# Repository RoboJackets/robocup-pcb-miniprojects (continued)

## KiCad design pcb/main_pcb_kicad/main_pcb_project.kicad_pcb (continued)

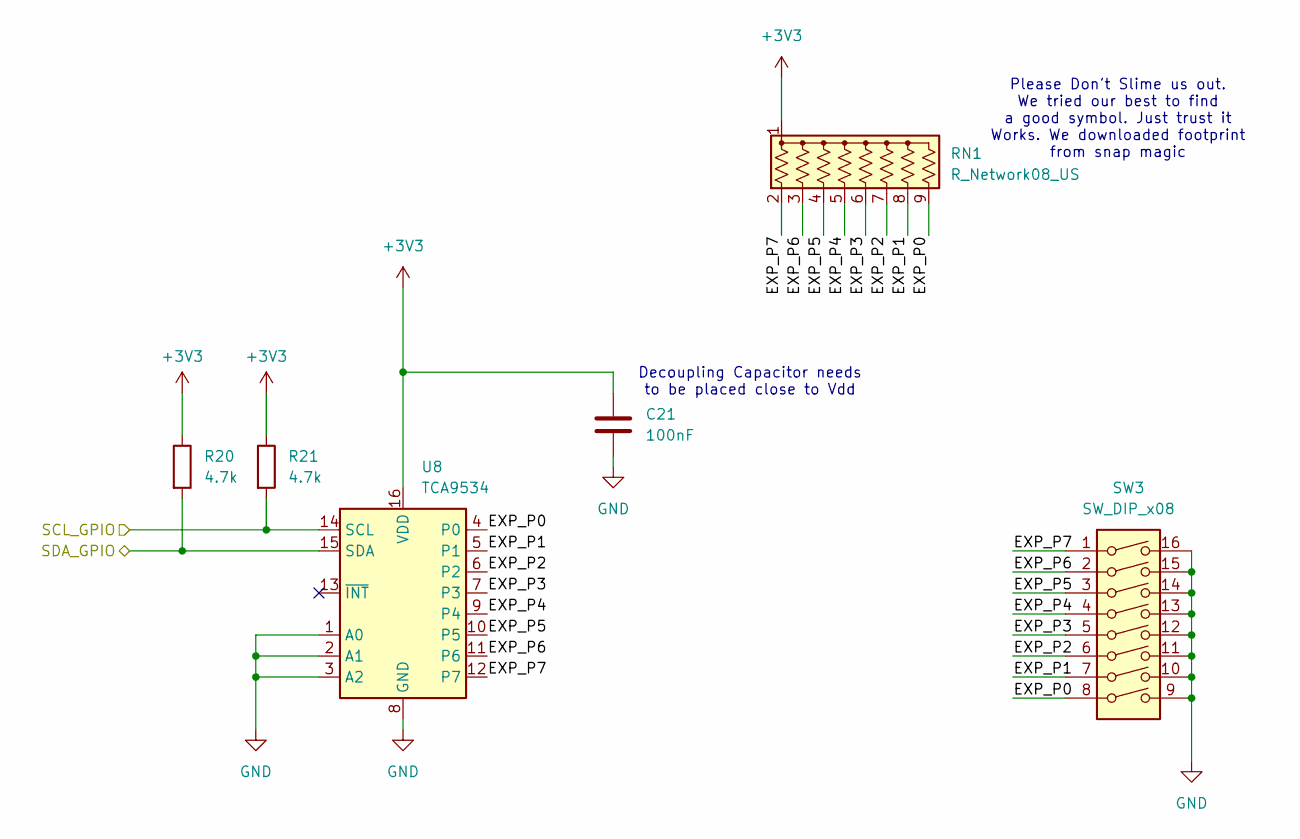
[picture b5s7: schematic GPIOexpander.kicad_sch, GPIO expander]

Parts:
C21: 100nF; C_0603_1608Metric; Manufacturer P/N CL10B104KB8NNNC
R20, R21: 4.7k; R_0402_1005Metric; Manufacturer P/N RC0402FR-074K7L
RN1: R_Network08_US; YC158_RNet08; Manufacturer P/N RC0402FR-074K7L
SW3: SW_DIP_x08; SW_DIP_SPSTx08_Slide_9.78x22.5mm_W7.62mm_P2.54mm; Manufacturer P/N DS01C-254-L-08BE
U8: TCA9534; TSSOP-16_4.4x5mm_P0.65mm; Manufacturer P/N TCA9534PWR

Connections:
+3V3: C21.1, R20.1, R21.1, RN1.1 (common), U8.16 (VDD); also elsewhere on the board
/GPIO expander/EXP_P0: RN1.9 (R8), SW3.8, U8.4 (P0)
/GPIO expander/EXP_P1: RN1.8 (R7), SW3.7, U8.5 (P1)
/GPIO expander/EXP_P2: RN1.7 (R6), SW3.6, U8.6 (P2)
/GPIO expander/EXP_P3: RN1.6 (R5), SW3.5, U8.7 (P3)
/GPIO expander/EXP_P4: RN1.5 (R4), SW3.4, U8.9 (P4)
/GPIO expander/EXP_P5: RN1.4 (R3), SW3.3, U8.10 (P5)
/GPIO expander/EXP_P6: RN1.3 (R2), SW3.2, U8.11 (P6)
/GPIO expander/EXP_P7: RN1.2 (R1), SW3.1, U8.12 (P7)
/SCL_GPIO: R21.2, U8.14 (SCL); also elsewhere on the board
/SDA_GPIO: R20.2, U8.15 (SDA); also elsewhere on the board
GND: C21.2, SW3.9, SW3.10, SW3.11, SW3.12, SW3.13, SW3.14, SW3.15, SW3.16, U8.1 (A0), U8.2 (A1), U8.3 (A2), U8.8 (GND); also elsewhere on the board

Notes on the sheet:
Decoupling Capacitor needs to be placed close to Vdd
Please Don't Slime us out. We tried our best to find a good symbol. Just trust it Works. We downloaded footprint from snap magic

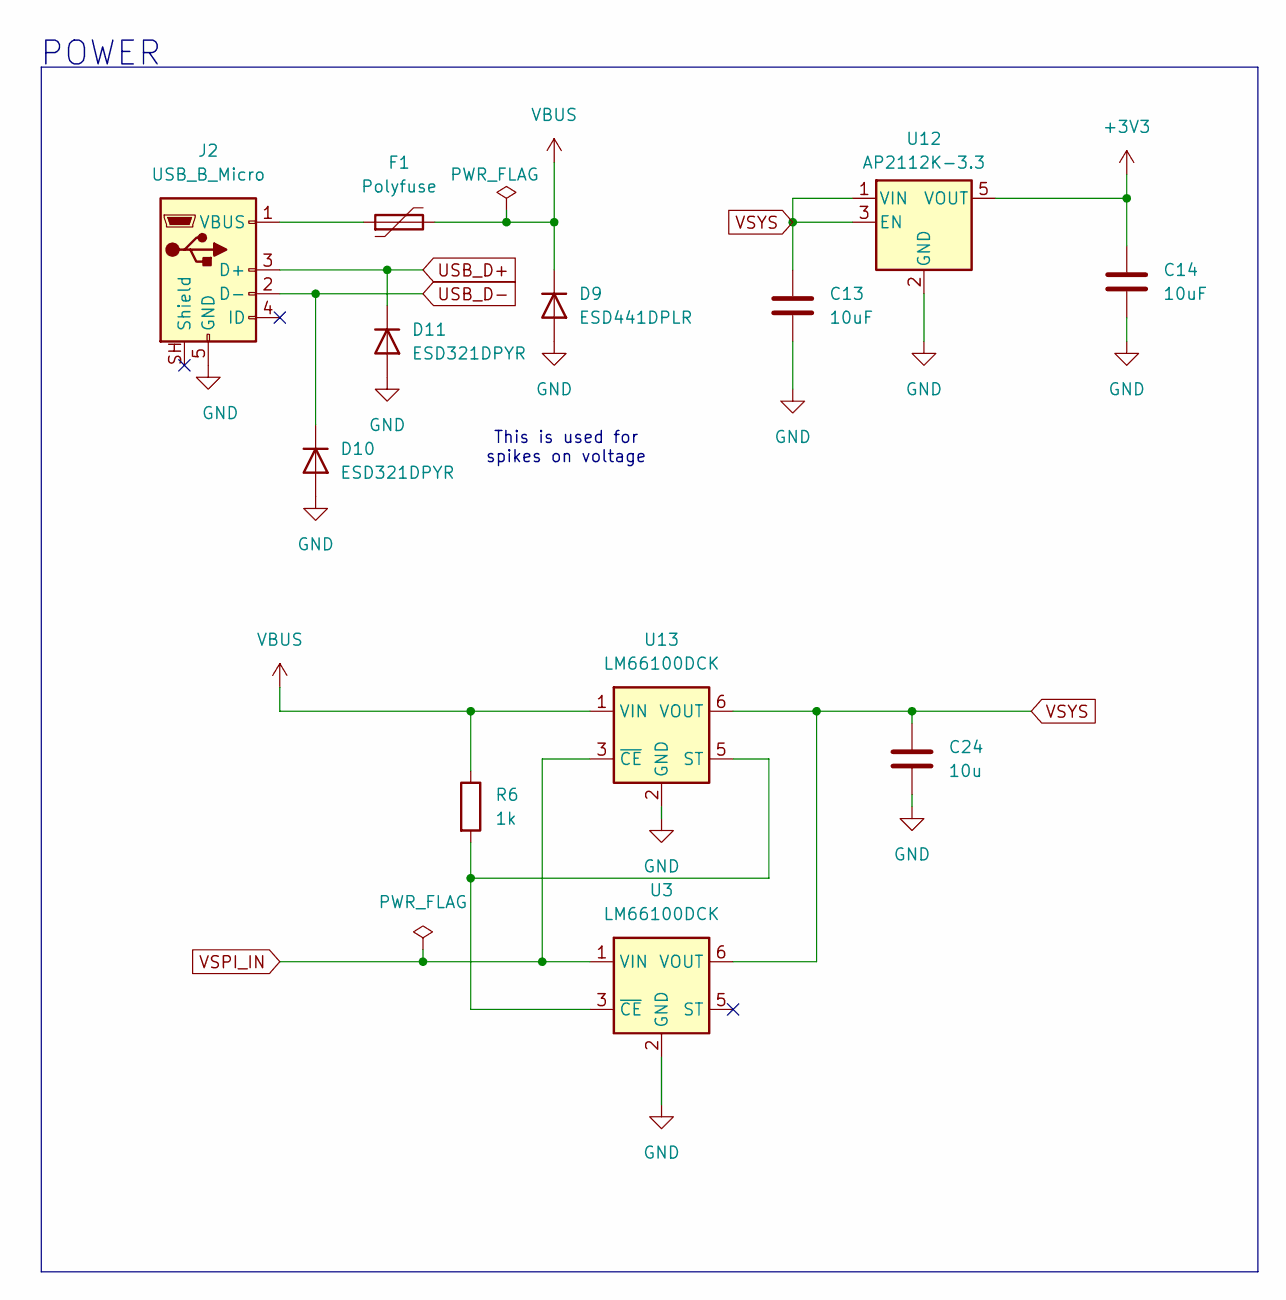
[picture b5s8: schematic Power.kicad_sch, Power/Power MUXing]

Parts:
C13, C14: 10uF; C_0402_1005Metric; Manufacturer P/N C0805C106M4PACTU
C24: 10u; C_0402_1005Metric; Manufacturer P/N C0805C106M4PACTU
D9: ESD441DPLR; D_0201_0603Metric; Manufacturer P/N ESD441DPLR
D10, D11: ESD321DPYR; D_0402_1005Metric; Manufacturer P/N ESD351DPYR
F1: Polyfuse; Fuse_1206_3216Metric; Manufacturer P/N 0ZCJ0050FF2G
J2: USB_B_Micro; USB_Micro-B_Amphenol_10118194_Horizontal; Manufacturer P/N 10118194-0001LF
R6: 1k; R_0402_1005Metric; Manufacturer P/N RC0402FR-071KL
U3, U13: LM66100DCK; SOT-363_SC-70-6; Manufacturer P/N LM66100DCKR
U12: AP2112K-3.3; SOT-23-5; Manufacturer P/N AP2112K-3.3TRG1

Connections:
+3V3: C14.1, U12.5 (VOUT); also elsewhere on the board
GND: C13.2, C14.2, C24.2, D9.2 (A), D10.2 (A), D11.2 (A), J2.5 (GND), U3.2 (GND), U12.2 (GND), U13.2 (GND); also elsewhere on the board
unnamed: F1.1, J2.1 (VBUS)
unnamed: R6.2, U3.3 (~CE), U13.5 (ST)
USB_D+: D11.1 (K), J2.3 (D+); also elsewhere on the board
USB_D-: D10.1 (K), J2.2 (D-); also elsewhere on the board
VBUS: D9.1 (K), F1.2, R6.1, U13.1 (VIN); also elsewhere on the board
VSPI_IN: U3.1 (VIN), U13.3 (~CE); also elsewhere on the board
VSYS: C13.1, C24.1, U3.6 (VOUT), U12.1 (VIN), U12.3 (EN), U13.6 (VOUT); also elsewhere on the board

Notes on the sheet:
POWER
This is used for spikes on voltage

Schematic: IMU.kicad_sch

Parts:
C15: 0.1uF; C_0603_1608Metric; Manufacturer P/N CL10B104KB8NNNC
C16: 2.2uF; C_0603_1608Metric; Manufacturer P/N CL10B225KP8NNNC
C17: 10nF; C_0603_1608Metric; Manufacturer P/N CL10B103KB8NNNC
R12, R13: 4.7k; R_0402_1005Metric; Manufacturer P/N RC0402FR-074K7L
U4: ICM-42605; LGA14_2P5X3X0P91_IVS-L; Manufacturer P/N ICM-42605

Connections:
+3V3: C15.1, C16.1, C17.1, R12.1, R13.1, U4.5 (VDDIO), U4.8 (VDD), U4.12 (AP_CS); also elsewhere on the board
/SCL_IMU: R12.2, U4.13 (AP_SCL/AP_SCLK); also elsewhere on the board
/SDA_IMU: R13.2, U4.14 (AP_SDA/AP_SDIO/AP_SDI); also elsewhere on the board
GND: C15.2, C16.2, C17.2, U4.1 (AP_SDO/AP_AD0), U4.6 (GND), U4.7 (RESV), U4.9 (INT2/FSYNC); also elsewhere on the board

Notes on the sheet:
These are pull up resistors
Please don't slime us out. We tried our best to make another design but things happened and we were unable Sorry :(
These capacitors need to be placed close to Vdd
Place capacitor close to VDDIO

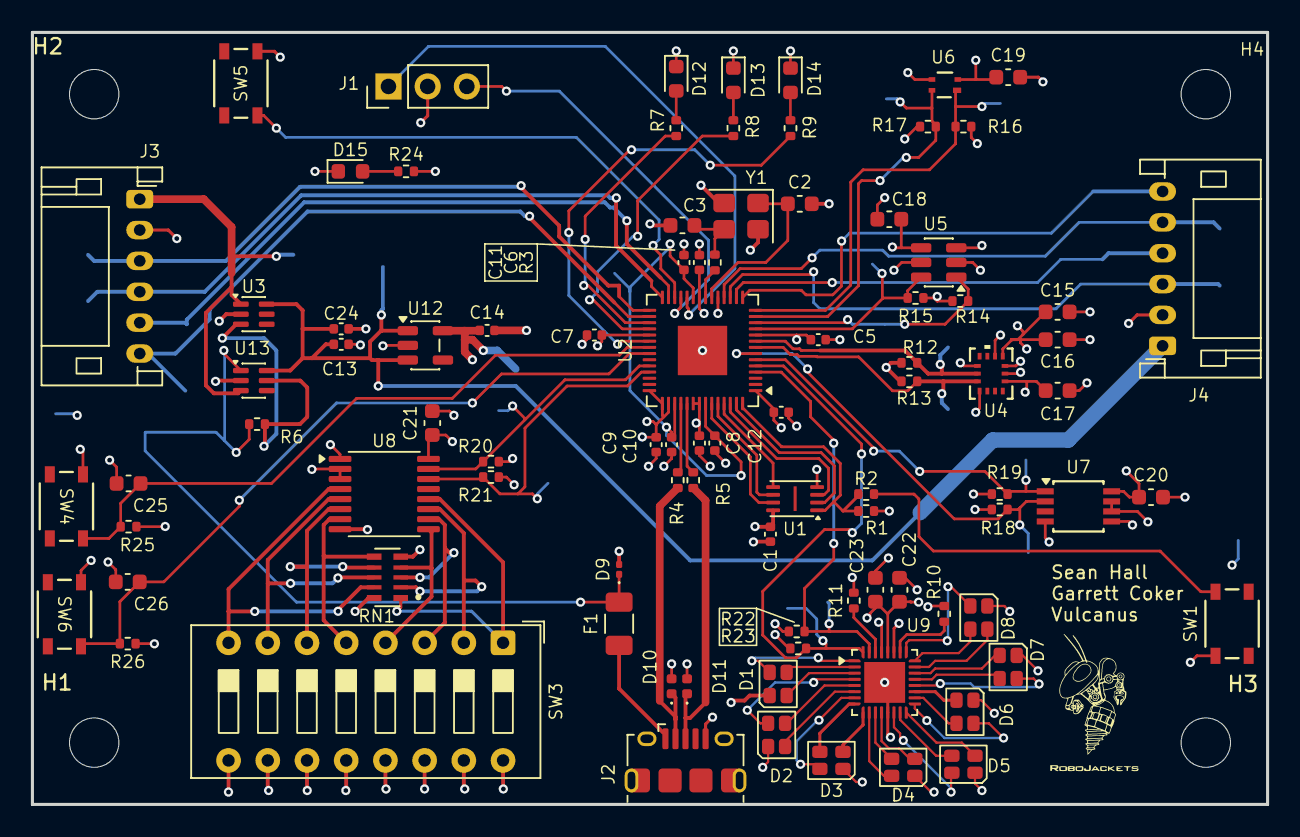
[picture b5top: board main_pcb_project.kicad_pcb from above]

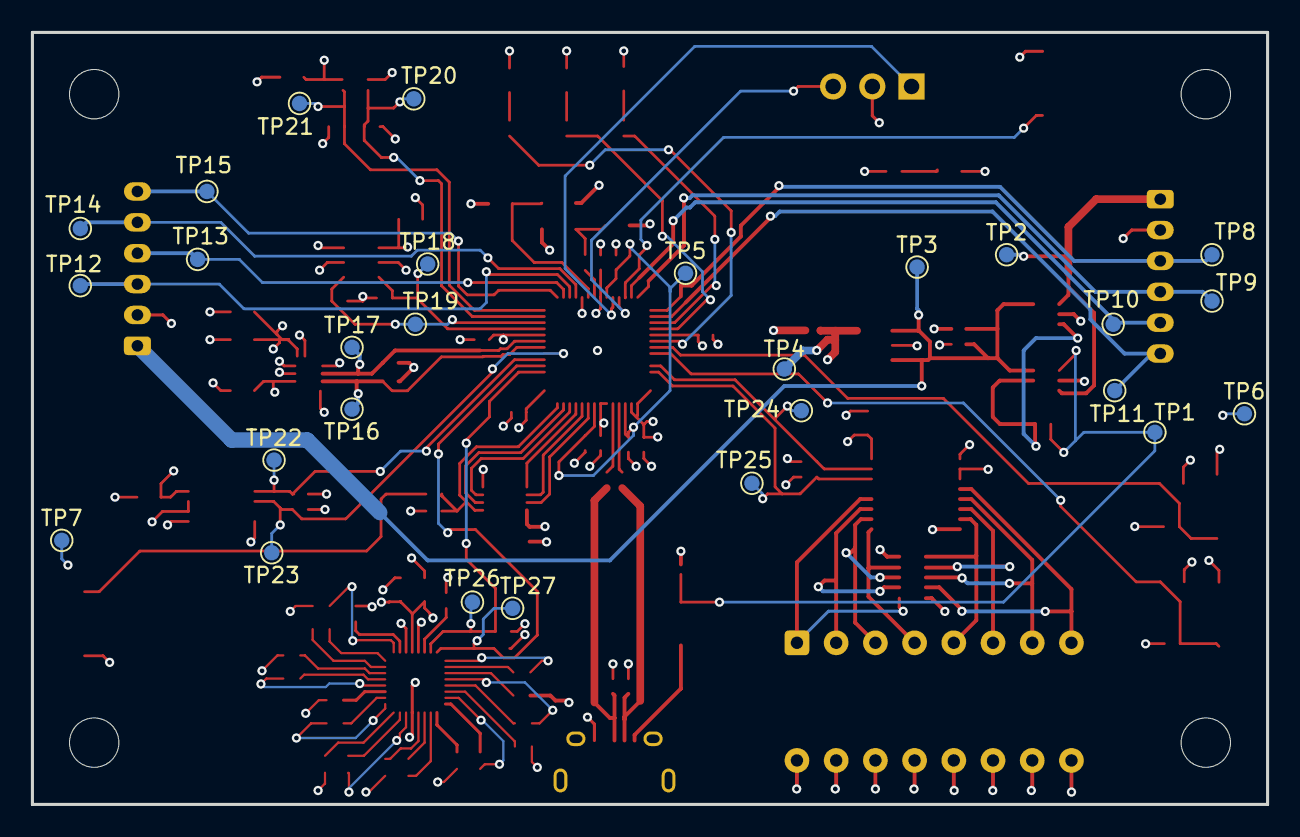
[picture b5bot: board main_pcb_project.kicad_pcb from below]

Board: 4 copper layers, 80.0 x 50.0 mm, 121 parts (27 on the bottom side), 88 nets.

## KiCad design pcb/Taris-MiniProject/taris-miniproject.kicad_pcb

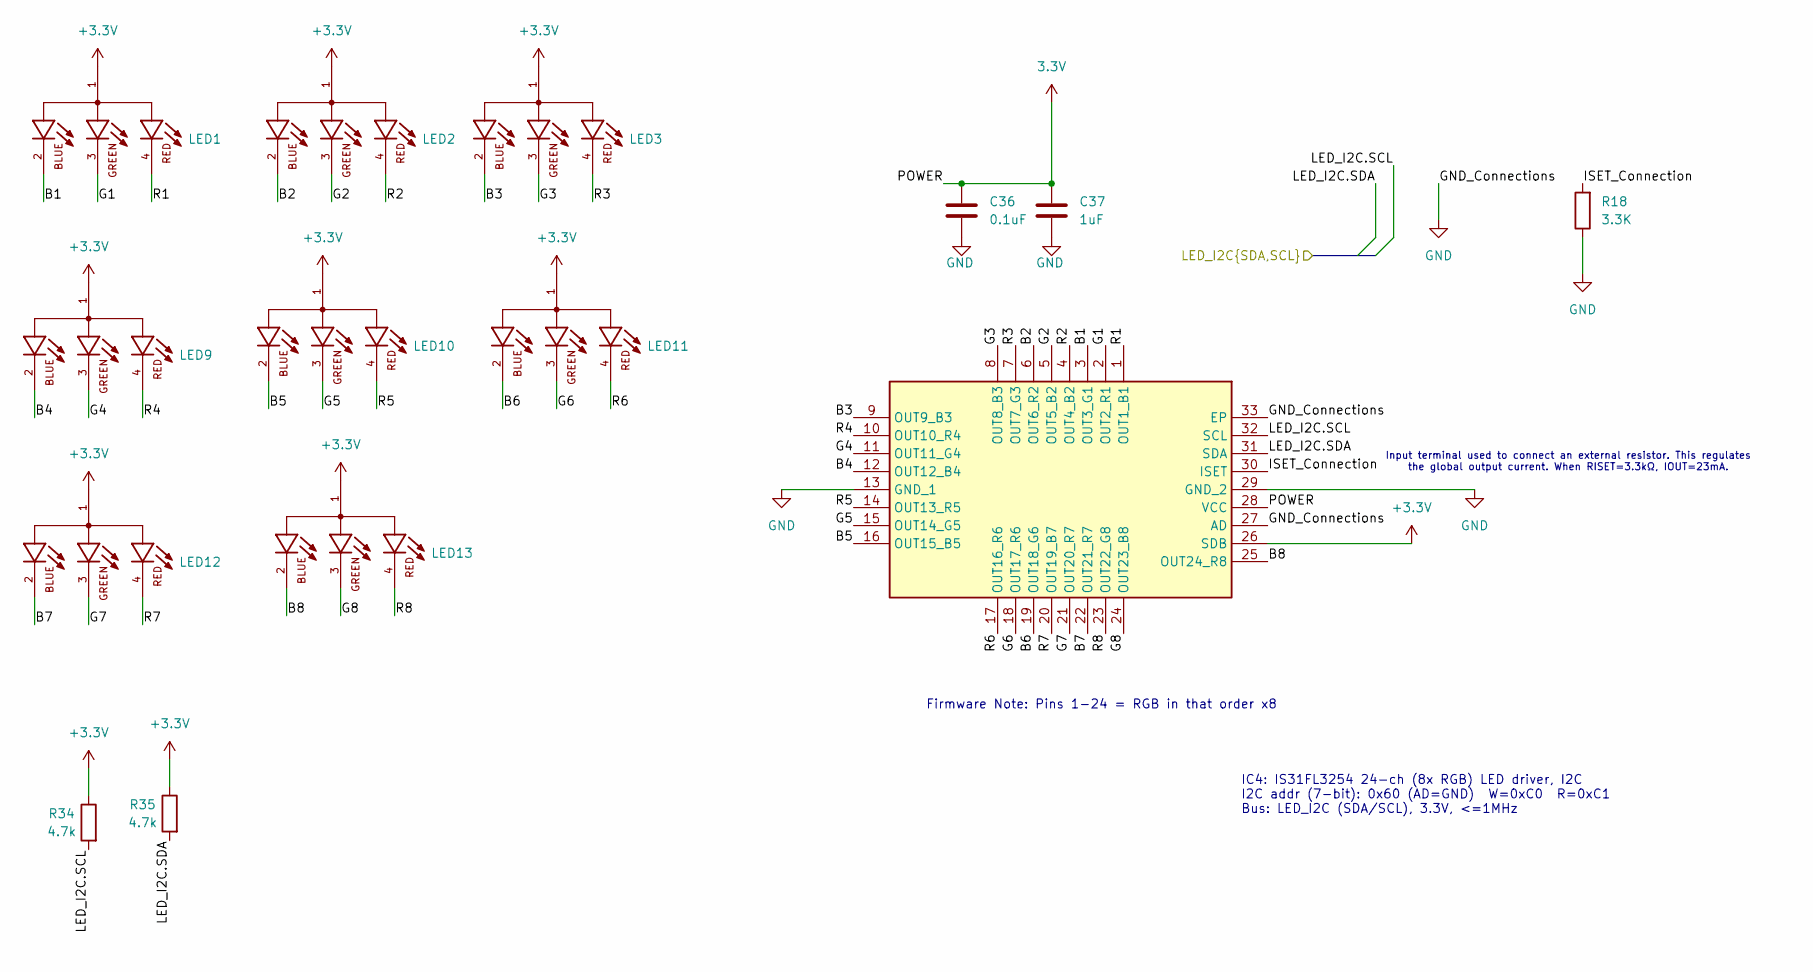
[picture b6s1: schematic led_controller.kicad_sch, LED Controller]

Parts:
C36: 0.1uF; C_0603_1608Metric; Manufacturer P/N CC0603KRX5R8BB104
C37: 1uF; C_0603_1608Metric; Manufacturer P/N GMC04X7R105K10NT
IC4: IS31FL3254-QFLS4-TR; QFN40P400X400X80-33N-D; Manufacturer_Part_Number IS31FL3254-QFLS4-TR
LED1, LED2, LED3, LED9, LED10, LED11, LED12, LED13: CLMVC-FKA-CL1D1L71BB7C3C3; LED_CLMVC-FKA-CL1D1L71BB7C3C3; PARTREV 14; DigiKey_Part_Number CLMVC-FKA-CL1D1L71BB7C3C3CT-ND
R18: 3.3K; R_0603_1608Metric; Manufacturer P/N RC0603FR-073K3L
R34, R35: 4.7k; R_0402_1005Metric; Manufacturer P/N RC0402FR-134K7L

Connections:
3.3V: C36.1, C37.1, IC4.28 (VCC); also elsewhere on the board
+3.3V: IC4.26 (SDB), LED1.1, LED2.1, LED3.1, LED9.1, LED10.1, LED11.1, LED12.1, LED13.1, R34.1, R35.1; also elsewhere on the board
/LED Controller/B1: IC4.3 (OUT3_G1), LED1.2
/LED Controller/B2: IC4.6 (OUT6_R2), LED2.2
/LED Controller/B3: IC4.9 (OUT9_B3), LED3.2
/LED Controller/B4: IC4.12 (OUT12_B4), LED9.2
/LED Controller/B5: IC4.16 (OUT15_B5), LED10.2
/LED Controller/B6: IC4.19 (OUT18_G6), LED11.2
/LED Controller/B7: IC4.22 (OUT21_R7), LED12.2
/LED Controller/B8: IC4.25 (OUT24_R8), LED13.2
/LED Controller/G1: IC4.2 (OUT2_R1), LED1.3
/LED Controller/G2: IC4.5 (OUT5_B2), LED2.3
/LED Controller/G3: IC4.8 (OUT8_B3), LED3.3
/LED Controller/G4: IC4.11 (OUT11_G4), LED9.3
/LED Controller/G5: IC4.15 (OUT14_G5), LED10.3
/LED Controller/G6: IC4.18 (OUT17_R6), LED11.3
/LED Controller/G7: IC4.21 (OUT20_R7), LED12.3
/LED Controller/G8: IC4.24 (OUT23_B8), LED13.3
/LED Controller/ISET_Connection: IC4.30 (ISET), R18.2
/LED Controller/R1: IC4.1 (OUT1_B1), LED1.4
/LED Controller/R2: IC4.4 (OUT4_B2), LED2.4
/LED Controller/R3: IC4.7 (OUT7_G3), LED3.4
/LED Controller/R4: IC4.10 (OUT10_R4), LED9.4
/LED Controller/R5: IC4.14 (OUT13_R5), LED10.4
/LED Controller/R6: IC4.17 (OUT16_R6), LED11.4
/LED Controller/R7: IC4.20 (OUT19_B7), LED12.4
/LED Controller/R8: IC4.23 (OUT22_G8), LED13.4
/LED_I2C.SCL: IC4.32 (SCL), R34.2; also elsewhere on the board
/LED_I2C.SDA: IC4.31 (SDA), R35.2; also elsewhere on the board
GND: C36.2, C37.2, IC4.13 (GND_1), IC4.27 (AD), IC4.29 (GND_2), IC4.33 (EP), R18.1; also elsewhere on the board

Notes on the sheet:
Firmware Note: Pins 1-24 = RGB in that order x8
IC4: IS31FL3254 24-ch (8x RGB) LED driver, I2C I2C addr (7-bit): 0x60 (AD=GND) W=0xC0 R=0xC1 Bus: LED_I2C (SDA/SCL), 3.3V, <=1MHz
Input terminal used to connect an external resistor. This regulates the global output current. When RISET=3.3kΩ, IOUT=23mA.

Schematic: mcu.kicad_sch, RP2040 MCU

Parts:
C1, C2: 1u; C_0402_1005Metric; Manufacturer P/N GRM155Z71A105KE01J
C3, C4, C5, C6, C7, C8, C9, C10, C11, C14: 100nF; C_0402_1005Metric; Manufacturer P/N CC0603KRX5R8BB104
C12, C13: 15p; C_0402_1005Metric; Manufacturer P/N GRM1555C1H150JA01D
D1, D2: RED; LED_0603_1608Metric; Manufacturer P/N LTST-C190KRKT
J3, J4: Conn_01x06; JST_PH_S6B-PH-K_1x06_P2.00mm_Horizontal; Manufacturer P/N S6B-PH-K-S
R1, R3: 1k; R_0402_1005Metric; Manufacturer P/N RC0402FR-071KL
R2, R6, R11, R12: 10k; R_0402_1005Metric; Manufacturer P/N RC0402FR-0710KL
R4, R5: 27.4; R_0402_1005Metric; Manufacturer P/N RC0402FR-0727R4L
SW1, SW2: PTS810; SW_SPST_PTS810; Manufacturer P/N PTS810SJK250SMTR LFS
U1: RP2040; QFN-56-1EP_7x7mm_P0.4mm_EP3.2x3.2mm; Manufacturer P/N SC0914(13)
U2: W25Q16JVSS; SOIC-8_5.3x5.3mm_P1.27mm; Manufacturer P/N W25Q16JVSSIQ
Y1: ABM8-272-T3; Crystal_SMD_Abracon_ABM8AIG-4Pin_3.2x2.5mm; Manufacturer P/N ABM8-272-T3

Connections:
+1.1V: C1.1, C3.1, C4.1, U1.23 (DVDD), U1.45 (VREG_VOUT), U1.50 (DVDD)
+3.3V: C2.1, C5.1, C6.1, C7.1, C8.1, C9.1, C10.1, C11.1, C14.1, R2.1, R6.2, U1.1 (IOVDD), U1.10 (IOVDD), U1.22 (IOVDD), U1.33 (IOVDD), U1.42 (IOVDD), U1.43 (ADC_AVDD), U1.44 (VREG_VIN), U1.48 (USB_VDD), U1.49 (IOVDD), U2.8 (VCC); also elsewhere on the board
/Color_I2C.SCL: U1.16 (GPIO13); also elsewhere on the board
/Color_I2C.SDA: U1.15 (GPIO12); also elsewhere on the board
/GPIO_I2C.SCL: U1.30 (GPIO19); also elsewhere on the board
/GPIO_I2C.SDA: U1.29 (GPIO18); also elsewhere on the board
/Hall_I2C.SCL: U1.28 (GPIO17); also elsewhere on the board
/Hall_I2C.SDA: U1.27 (GPIO16); also elsewhere on the board
/IMU_I2C.SCL: U1.37 (GPIO25); also elsewhere on the board
/IMU_I2C.SDA: U1.36 (GPIO24); also elsewhere on the board
/IMU_Sensor_I2C.SCL: U1.35 (GPIO23); also elsewhere on the board
/IMU_Sensor_I2C.SDA: U1.34 (GPIO22); also elsewhere on the board
/LED_I2C.SCL: U1.18 (GPIO15); also elsewhere on the board
/LED_I2C.SDA: U1.17 (GPIO14); also elsewhere on the board
/MCU/QSPI_CLK: U1.52 (QSPI_SCLK), U2.6 (CLK)
/MCU/QSPI_SD0: U1.53 (QSPI_SD0), U2.5 (DI/IO_{0})
/MCU/QSPI_SD1: U1.55 (QSPI_SD1), U2.2 (DO/IO_{1})
/MCU/QSPI_SD2: U1.54 (QSPI_SD2), U2.3 (~WP/IO_{2})
/MCU/QSPI_SD3: U1.51 (QSPI_SD3), U2.7 (~HOLD/~RESET/IO_{3})
/MCU/gp_btn_a: U1.2 (GPIO0); also elsewhere on the board
/MCU/gp_btn_b: U1.3 (GPIO1); also elsewhere on the board
/MCU/gp_led_a: R11.1, U1.4 (GPIO2)
/MCU/gp_led_b: R12.1, U1.5 (GPIO3)
/MCU/master_csn: J4.5, U1.7 (GPIO5)
/MCU/master_rx: J4.4, U1.6 (GPIO4)
/MCU/master_sck: J4.6, U1.8 (GPIO6)
/MCU/master_tx: J4.3, U1.9 (GPIO7)
/MCU/slave_csn: J3.5, U1.12 (GPIO9)
/MCU/slave_rx: J3.4, U1.11 (GPIO8)
/MCU/slave_sck: J3.6, U1.13 (GPIO10)
/MCU/slave_tx: J3.3, U1.14 (GPIO11)
/MCU/~QSPI_CS: R2.2, R3.1, U1.56 (~QSPI_SS), U2.1 (~CS)
/MCU/~RESET: R6.1, SW1.2 (B), U1.26 (RUN)
/MCU/~USB_BOOT: R3.2, SW2.2 (B)
/SLAVE_POWER: J3.2; also elsewhere on the board
/SPI_MASTER_INPUT: J4.2; also elsewhere on the board
/SWD.CLK: U1.24 (SWCLK); also elsewhere on the board
/SWD.DIO: U1.25 (SWDIO); also elsewhere on the board
/Temp_I2C.SCL: U1.32 (GPIO21); also elsewhere on the board
/Temp_I2C.SDA: U1.31 (GPIO20); also elsewhere on the board
/USB.DM: R4.1; also elsewhere on the board
/USB.DP: R5.1; also elsewhere on the board
GND: C1.2, C2.2, C3.2, C4.2, C5.2, C6.2, C7.2, C8.2, C9.2, C10.2, C11.2, C12.1, C13.1, C14.2, D1.1 (K), D2.1 (K), J3.1, J4.1, SW1.1 (A), SW2.1 (A), U1.19 (TESTEN), U1.57 (GND), U2.4 (GND), Y1.2 (G), Y1.4 (G); also elsewhere on the board
unnamed: C13.2, R1.2, Y1.3
unnamed: D1.2 (A), R11.2
unnamed: D2.2 (A), R12.2
unnamed: R4.2, U1.46 (USB_DM)
unnamed: R5.2, U1.47 (USB_DP)
unnamed: C12.2, U1.20 (XIN), Y1.1
unnamed: R1.1, U1.21 (XOUT)

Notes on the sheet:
V_{F} (typ) = 2 V R = 10 kΩ V = (3.3 - 2) I = 0.13 mA These don't need to be very bright
General-Purpose Debug Buttons
This causes the MCU to load from USB than flash
2 MB Flash
RP2040 MCU + Support Circuitry
This button causes the MCU to enter a reset state
MCU Debug Buttons
Place 100n caps near power pins
SPI Connectors
General-Purpose Debug LEDs
Place 1u caps near VREG_VIN/OUT
27.4R close to USB pins

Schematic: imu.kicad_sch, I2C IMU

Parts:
C19, C20: 100nF; C_0402_1005Metric; Manufacturer P/N CC0603KRX5R8BB104
R22, R23: 4.7k; R_0402_1005Metric; Manufacturer P/N RC0402FR-134K7L
U6: LSM6DSM; LGA-14_3x2.5mm_P0.5mm_LayoutBorder3x4y; Manufacturer P/N LSM6DSMTR

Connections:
+3.3V: C19.1, C20.1, R22.1, R23.1, U6.5 (VDDIO), U6.8 (VDD), U6.12 (CS); also elsewhere on the board
/IMU_I2C.SCL: R23.2, U6.13 (SCL); also elsewhere on the board
/IMU_I2C.SDA: R22.2, U6.14 (SDA); also elsewhere on the board
GND: C19.2, C20.2, U6.1 (SDO/SA0), U6.2 (SDX), U6.3 (SCX), U6.6 (GND), U6.7 (GND); also elsewhere on the board

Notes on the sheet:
I2C IMU

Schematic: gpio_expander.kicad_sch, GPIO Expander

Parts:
C21: 100nF; C_0603_1608Metric; Manufacturer P/N CC0603KRX5R8BB104
R28, R29: 4.7k; R_0402_1005Metric; Manufacturer P/N RC0402FR-134K7L
RN1: YC158TJR-0710KL; RESCAXE64P320X160X70-10N; Manufacturer P/N YC158TJR-0710KL
S2: DS01C-254-L-08BE; SW_DS01C-254-L-08BE; PARTREV 1.0
U7: TCA9534PWR; SOP65P640X120-16N; PARTREV D

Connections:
3.3V: C21.1, RN1.5, RN1.10, U7.16 (VCC); also elsewhere on the board
+3.3V: R28.1, R29.1; also elsewhere on the board
/GPIO Expander/Switch1: RN1.1, S2.1A, U7.4 (P0)
/GPIO Expander/Switch2: RN1.2, S2.2A, U7.5 (P1)
/GPIO Expander/Switch 3: RN1.3, S2.3A, U7.6 (P2)
/GPIO Expander/Switch 4: RN1.4, S2.4A, U7.7 (P3)
/GPIO Expander/Switch 5: RN1.6, S2.5A, U7.9 (P4)
/GPIO Expander/Switch 6: RN1.7, S2.6A, U7.10 (P5)
/GPIO Expander/Switch 7: RN1.8, S2.7A, U7.11 (P6)
/GPIO Expander/Switch 8: RN1.9, S2.8A, U7.12 (P7)
/GPIO_I2C.SCL: R28.2, U7.14 (SCL); also elsewhere on the board
/GPIO_I2C.SDA: R29.2, U7.15 (SDA); also elsewhere on the board
GND: C21.2, S2.1B, S2.2B, S2.3B, S2.4B, S2.5B, S2.6B, S2.7B, S2.8B, U7.1 (A0), U7.2 (A1), U7.3 (A2), U7.8 (GND); also elsewhere on the board

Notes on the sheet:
U7: TCA9534 8-bit I2C GPIO expander I2C addr (7-bit): 0x20 (A2:A0 = GND) W=0x40 R=0x41 Bus: GPIO_I2C (SDA/SCL), 3.3V, <=400kHz INT: NOT CONNECTED
GPIO Expander

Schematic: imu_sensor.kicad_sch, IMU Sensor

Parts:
C28: 10nF; C_0603_1608Metric; Manufacturer P/N GMC10X7R103K50NT
C30: 0.1uF; C_0603_1608Metric; Manufacturer P/N CC0603KRX5R8BB104
C35: 2.2uF; C_0603_1608Metric; Manufacturer P/N GMC10X7R225K25NT
R32, R33: 4.7k; R_0402_1005Metric; Manufacturer P/N RC0402FR-134K7L
U13: ICM-42605; LGA14_2P5X3X0P91_IVS; Manufacturer P/N ICM-42605

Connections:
3.3V: C28.1, C30.1, C35.1, U13.1 (AP_SDO/AP_AD0), U13.5 (VDDIO), U13.8 (VDD), U13.12 (AP_CS); also elsewhere on the board
+3.3V: R32.1, R33.1; also elsewhere on the board
/IMU_Sensor_I2C.SCL: R33.2, U13.13 (AP_SCL/AP_SCLK); also elsewhere on the board
/IMU_Sensor_I2C.SDA: R32.2, U13.14 (AP_SDA/AP_SDIO/AP_SDI); also elsewhere on the board
GND: C28.2, C30.2, C35.2, U13.6 (GND), U13.9 (INT2/FSYNC); also elsewhere on the board

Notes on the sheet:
IMU
U13: ICM-42605 6-axis IMU, I2C I2C addr (7-bit): 0x69 (AD0=3V3) W=0xD2 R=0xD3 Bus: IMU_Sensor_I2C, 3.3V, <=1MHz

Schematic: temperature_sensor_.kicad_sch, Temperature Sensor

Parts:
C23: 100nF; C_0603_1608Metric; Manufacturer P/N CC0603KRX5R8BB104
IC1: LM75ADP,118; SOP65P490X110-8N; Manufacturer_Part_Number LM75ADP,118; Mouser Part Number 771-LM75ADP-T
R24, R25: 4.7k; R_0402_1005Metric; Manufacturer P/N RC0402FR-134K7L

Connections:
+3.3V: C23.1, IC1.8 (VCC), R24.1, R25.1; also elsewhere on the board
/Temp_I2C.SCL: IC1.2 (SCL), R25.2; also elsewhere on the board
/Temp_I2C.SDA: IC1.1 (SDA), R24.2; also elsewhere on the board
GND: C23.2, IC1.4 (GND), IC1.5 (A2), IC1.6 (A1), IC1.7 (A0); also elsewhere on the board

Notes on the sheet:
IC1: LM75A temperature sensor I2C addr: 0x48 (A2:A0 = GND) Bus: Temp_I2C (SDA/SCL) 3.3 volts SCL period = 2.5 us 1/2.5us = 400kHz
Temperature Sensor

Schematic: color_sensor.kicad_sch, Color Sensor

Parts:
C27: 100nF; C_0603_1608Metric; Manufacturer P/N CC0603KRX5R8BB104
R30, R31: 4.7k; R_0402_1005Metric; Manufacturer P/N RC0402FR-134K7L
U12: VEML3328; Manufacturer P/N VEML3328

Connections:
3.3V: C27.1, U12.4 (VDD); also elsewhere on the board
+3.3V: R30.1, R31.1; also elsewhere on the board
/Color_I2C.SCL: R31.2, U12.3 (SCL); also elsewhere on the board
/Color_I2C.SDA: R30.2, U12.2 (SDA); also elsewhere on the board
GND: C27.2, U12.1 (GND); also elsewhere on the board

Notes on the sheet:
Color Sensor
U12: VEML3328 RGB/IR color sensor, I2C I2C addr (7-bit): 0x10 W=0x20 R=0x21 Bus: Color_I2C (SDA/SCL), 3.3V, <=400kHz

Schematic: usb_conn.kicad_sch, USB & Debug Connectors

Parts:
C17, C18, C24: 1u; C_0402_1005Metric; Manufacturer P/N GRM155Z71A105KE01J
J2: SWD; PinHeader_1x04_P2.54mm_Vertical; Manufacturer P/N 61300411121
J5: USB_B_Micro; USB_Micro-B_Amphenol_10118194-0001LF_Horizontal; Manufacturer P/N 10118194-0001LF
R13: 10K; R_0402_1005Metric; Manufacturer P/N RC0402FR-0710KL
U3: AP2112K-3.3; SOT-23-5; Manufacturer P/N AP2112K-3.3TRG1
U4, U5: USBLC6-2P6; SOT-666; Manufacturer P/N USBLC6-2SC6
U8, U9: LM66100DCK; SOT-363_SC-70-6; Manufacturer P/N LM66100DCKR

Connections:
+3.3V: C18.2, J2.1, U3.5 (VOUT), U5.5 (VBUS); also elsewhere on the board
/SLAVE_POWER: C17.2, C24.2, U3.1 (VIN), U3.3 (EN), U8.6 (VOUT), U9.6 (VOUT); also elsewhere on the board
/SPI_MASTER_INPUT: U8.3 (~CE), U9.1 (VIN); also elsewhere on the board
/SWD.CLK: U5.6 (I/O1); also elsewhere on the board
/SWD.DIO: U5.4 (I/O2); also elsewhere on the board
/USB.DM: U4.6 (I/O1); also elsewhere on the board
/USB.DP: U4.4 (I/O2); also elsewhere on the board
GND: C17.1, C18.1, C24.1, J2.4, J5.5 (GND), U3.2 (GND), U4.2 (GND), U5.2 (GND), U8.2 (GND), U9.2 (GND); also elsewhere on the board
unnamed: J2.2, U5.1 (I/O1)
unnamed: J2.3, U5.3 (I/O2)
unnamed: J5.3 (D+), U4.3 (I/O2)
unnamed: J5.2 (D-), U4.1 (I/O1)
unnamed: R13.1, U8.5 (ST), U9.3 (~CE)
VBUS: J5.1 (VBUS), R13.2, U4.5 (VBUS), U8.1 (VIN); also elsewhere on the board

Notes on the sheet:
SWD Debug Connector
Pull down resistor removed to avoid shorting the output. Capacitor kept so switching doesn't affect smoothness
Micro USB
MUX for SPI and Micro USB
3.3 V 600 mA LDO
0.5 mA of current when pulled low

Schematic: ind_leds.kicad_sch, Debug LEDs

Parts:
D3, D4, D5: RED; LED_0603_1608Metric; Manufacturer P/N LTST-C190KRKT
R15, R16, R17: 1k; R_0402_1005Metric; Manufacturer P/N RC0402FR-071KL

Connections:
3.3V: R17.2; also elsewhere on the board
/SLAVE_POWER: R16.2; also elsewhere on the board
GND: D3.1 (K), D4.1 (K), D5.1 (K); also elsewhere on the board
unnamed: D3.2 (A), R15.1
unnamed: D4.2 (A), R16.1
unnamed: D5.2 (A), R17.1
VBUS: R15.2; also elsewhere on the board

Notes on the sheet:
USB: 5 volts / 1 kOhm = 3.0 mA SPI_SLAVE_LED: 5 volts / 1 kOhm = 3.0 mA Color_Sensor_Power: 3.3 volts / 1 kOhm = 1.3 mA
Indicator LEDs

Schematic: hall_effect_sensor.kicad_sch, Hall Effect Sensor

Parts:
C22: 100nF; C_0603_1608Metric; Manufacturer P/N CC0603KRX5R8BB104
R26, R27: 4.7k; R_0402_1005Metric; Manufacturer P/N RC0402FR-134K7L
U11: TMAG5273C1QDBVR; SOT95P280X140-6N; PARTREV B

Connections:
3.3V: C22.1; also elsewhere on the board
+3.3V: R26.1, R27.1; also elsewhere on the board
/Hall_I2C.SCL: R26.2, U11.1 (SCL); also elsewhere on the board
/Hall_I2C.SDA: R27.2, U11.6 (SDA); also elsewhere on the board
GND: C22.2, U11.2 (GND), U11.3 (TEST), U11.4 (VCC); also elsewhere on the board

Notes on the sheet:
Hall Effect Sensor
U11: TMAG5273C1 3-axis Hall sensor, I2C I2C addr (7-bit): 0x78 (C1 default, VERIFY on HW) Bus: Hall_I2C (SDA/SCL), 3.3V, <=400kHz INT: NOT CONNECTED, set MASK_INTB=1 in firmware TEST: tied to GND (required)

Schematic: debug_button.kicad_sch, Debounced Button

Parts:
C15: 100nF; C_0402_1005Metric; Manufacturer P/N CC0603KRX5R8BB104
R7, R8: 10k; R_0402_1005Metric; Manufacturer P/N RC0402FR-0710KL
SW3: PTS810; SW_SPST_PTS810; Manufacturer P/N PTS810SJK250SMTR LFS

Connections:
+3.3V: SW3.1 (A); also elsewhere on the board
/MCU/gp_btn_a: C15.1, R8.2; also elsewhere on the board
GND: C15.2, R7.2; also elsewhere on the board
unnamed: R7.1, R8.1, SW3.2 (B)

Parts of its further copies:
C16: 100nF; C_0402_1005Metric; Manufacturer P/N CC0603KRX5R8BB104
R9, R10: 10k; R_0402_1005Metric; Manufacturer P/N RC0402FR-0710KL
SW4: PTS810; SW_SPST_PTS810; Manufacturer P/N PTS810SJK250SMTR LFS

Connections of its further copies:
+3.3V: SW4.1 (A); also elsewhere on the board
/MCU/gp_btn_b: C16.1, R10.2; also elsewhere on the board
GND: C16.2, R9.2; also elsewhere on the board
unnamed: R9.1, R10.1, SW4.2 (B)

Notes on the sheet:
RC low-pass filter -3 dB cutoff: 159.15 Hz

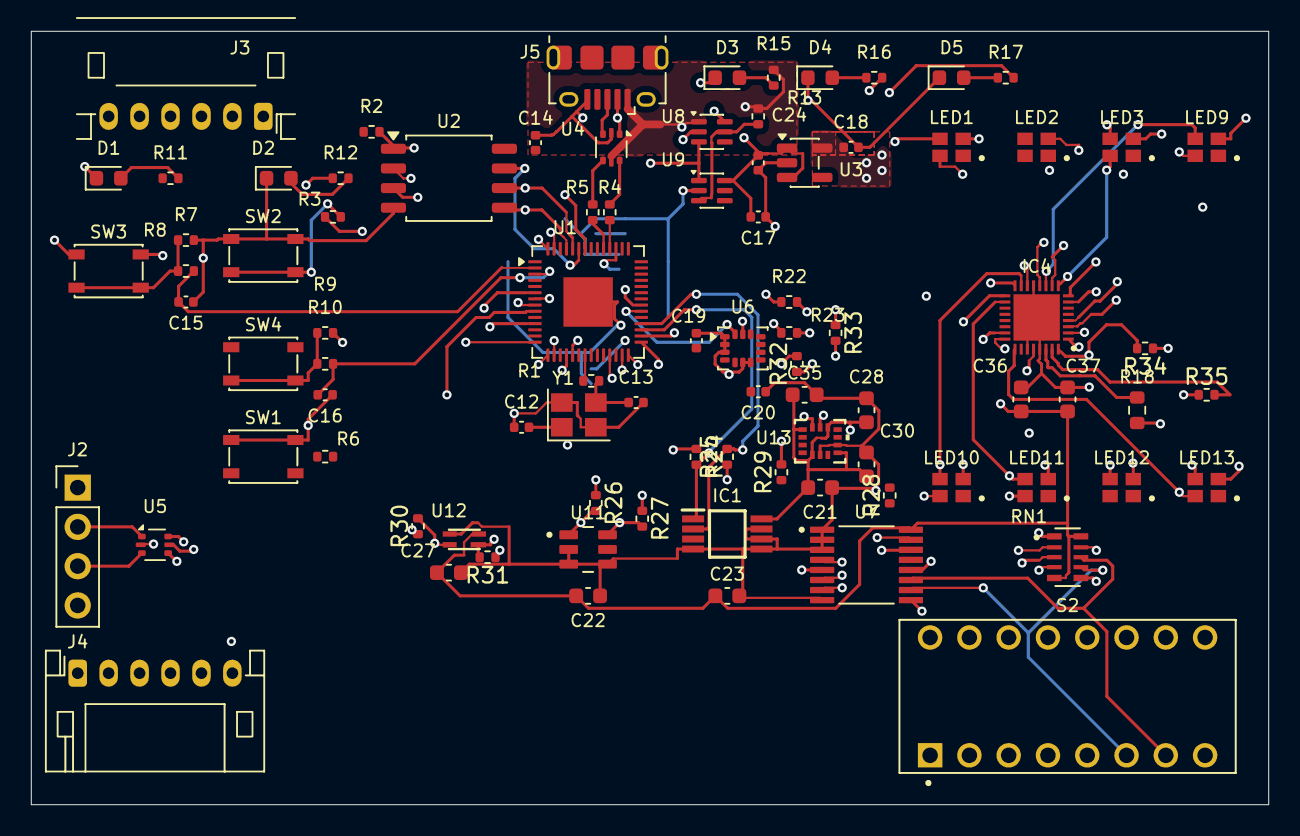
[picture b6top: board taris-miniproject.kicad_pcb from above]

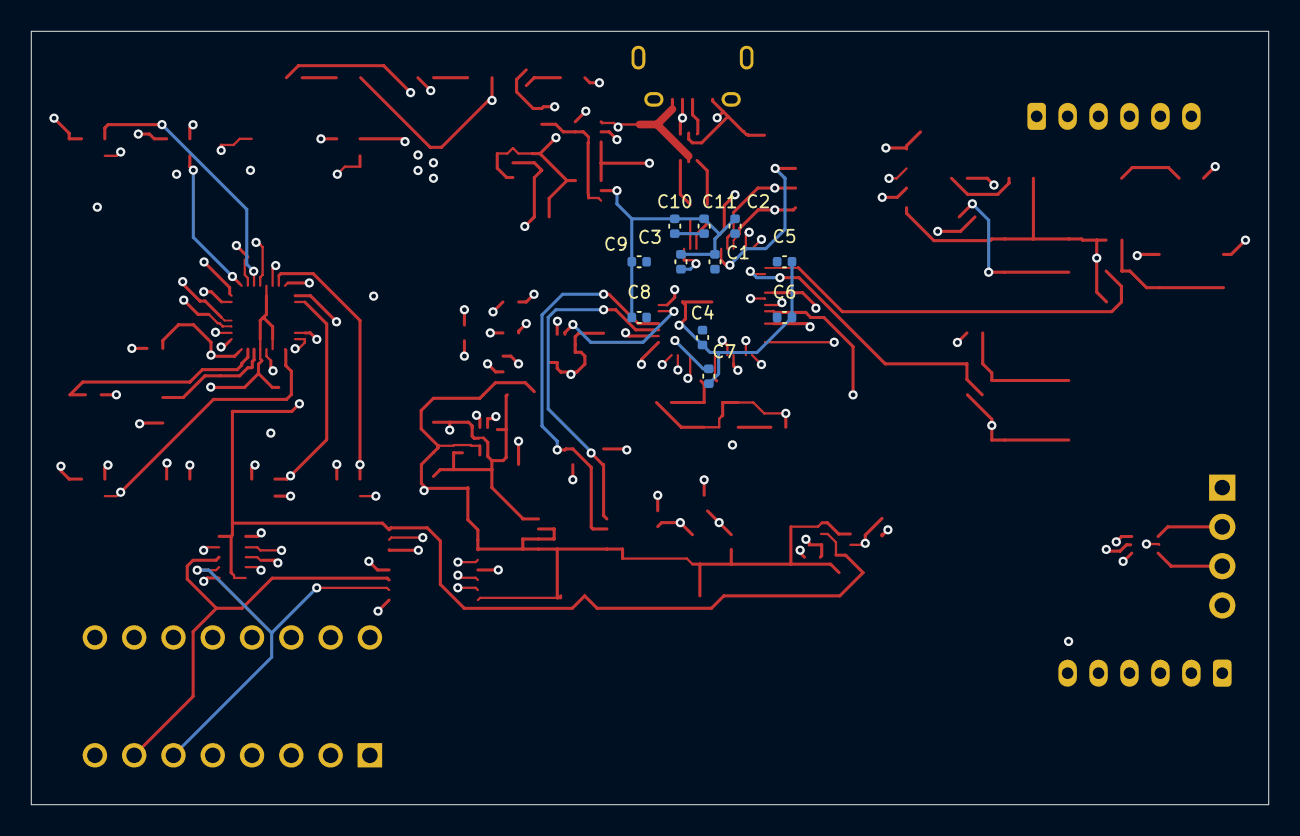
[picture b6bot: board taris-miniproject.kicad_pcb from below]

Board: 4 copper layers, 80.0 x 50.0 mm, 99 parts (11 on the bottom side), 95 nets.

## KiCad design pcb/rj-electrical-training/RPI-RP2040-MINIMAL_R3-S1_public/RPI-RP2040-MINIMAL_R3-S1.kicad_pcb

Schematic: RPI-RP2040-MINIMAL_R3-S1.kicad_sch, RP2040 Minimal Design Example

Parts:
C1, C4, C17: 10u; generic_capc2012x125; voltage 16V; tolerance 10%; part_uid RP-01GYSK-AVBE41
C2, C3: 15p; generic_capc1005x50; voltage 50V; tolerance 5%; part_uid RP-01C89W-LLY9XV
C5, C6, C7, C9, C11, C12, C13, C14, C15, C16: 100n; generic_capc1005x50; voltage 25V; tolerance 10%; part_uid RP-01BJ9Y-KRGF41
C8, C10: 1u; generic_capc1005x50; voltage 16V; tolerance 10%; part_uid RP-01GYSK-L7FEKV
J1: 10103594-0001LF; amphenol_10103594-0001lf; part_uid RP-019A1P-1JAX7V
J2: TSW-102-07-G-S; samtec_tsw-102-07-g-s; part_uid RP-01JV5X-LY21H5
J3, J4: TSW-118-07-L-D; samtec_tsw-118-07-l-d; part_uid RP-01JWH2-G371Y4
MH1, MH2, MH3, MH4: NPTH FD2.75mm SM3.15mm KO6mm; none_mh_npth_fd2p75mm_sm3p15mm_ko6mm; part_uid RP-01HF5R-LCTEJS
PCB1: R3; manufacturer_pn XXX
R1, R5: 1k; generic_resc1005x35; tolerance 1%; voltage 50V; part_uid RP-019A1P-4Z6ZWY
R2: 10k; generic_resc1005x35; tolerance 1%; voltage 50V; part_uid RP-019A1P-53DHSX; not fitted
R3, R4: 27; generic_resc1005x35; tolerance 1%; voltage 50V; part_uid RP-01C89V-LTEYC4
SBREV1: S1
U1: NCP1117ST33T3G; onsemi_ncp1117st33t3g; voltage 3.3V; part_uid RP-01JWD9-7JRX6J
U2: W25Q128JVSIQ; generic_soic127p790x195-8; voltage 2.7-3.6V; part_uid RP-01JWD4-F1H4N9
U3: RP2040; rpi_rp2040_vias; part_uid RP-01EKHS-ZTKTEH
VARIANT1: RPI-RP2040-MINIMAL
X1: 12MHz; generic_xtalcc320x250x80-4; tolerance 30ppm; part_uid RP-01G8X7-GS352B

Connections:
+1V1: C6.1, C7.1, C8.1, U3.23 (DVDD), U3.45 (VREG_VOUT), U3.50 (DVDD)
+3V3: C4.1, C5.1, C9.1, C10.1, C11.1, C12.1, C13.1, C14.1, C15.1, C16.1, C17.1, J3.2, R2.1, U1.2 (OUT), U1.4 (OUT), U2.8 (VCC), U3.1 (IOVDD), U3.10 (IOVDD), U3.22 (IOVDD), U3.33 (IOVDD), U3.42 (IOVDD), U3.43 (ADC_AVDD), U3.44 (VREG_IN), U3.48 (USB_VDD), U3.49 (IOVDD)
/GPIO0: J3.4, U3.2 (GPIO0)
/GPIO1: J3.6, U3.3 (GPIO1)
/GPIO2: J3.8, U3.4 (GPIO2)
/GPIO3: J3.10, U3.5 (GPIO3)
/GPIO4: J3.12, U3.6 (GPIO4)
/GPIO5: J3.14, U3.7 (GPIO5)
/GPIO6: J3.16, U3.8 (GPIO6)
/GPIO7: J3.18, U3.9 (GPIO7)
/GPIO8: J3.20, U3.11 (GPIO8)
/GPIO9: J3.22, U3.12 (GPIO9)
/GPIO10: J3.24, U3.13 (GPIO10)
/GPIO11: J3.26, U3.14 (GPIO11)
/GPIO12: J3.28, U3.15 (GPIO12)
/GPIO13: J3.30, U3.16 (GPIO13)
/GPIO14: J3.32, U3.17 (GPIO14)
/GPIO15: J3.34, U3.18 (GPIO15)
/GPIO16: J4.27, U3.27 (GPIO16)
/GPIO17: J4.25, U3.28 (GPIO17)
/GPIO18: J4.23, U3.29 (GPIO18)
/GPIO19: J4.21, U3.30 (GPIO19)
/GPIO20: J4.19, U3.31 (GPIO20)
/GPIO21: J4.17, U3.32 (GPIO21)
/GPIO22: J4.15, U3.34 (GPIO22)
/GPIO23: J4.13, U3.35 (GPIO23)
/GPIO24: J4.11, U3.36 (GPIO24)
/GPIO25: J4.9, U3.37 (GPIO25)
/GPIO26_ADC0: J4.7, U3.38 (GPIO26_ADC0)
/GPIO27_ADC1: J4.5, U3.39 (GPIO27_ADC1)
/GPIO28_ADC2: J4.3, U3.40 (GPIO28_ADC2)
/GPIO29_ADC3: J4.1, U3.41 (GPIO29_ADC3)
/QSPI_SCLK: U2.6 (CLK), U3.52 (QSPI_SCLK)
/QSPI_SD0: U2.5 (DI_IO0), U3.53 (QSPI_SD0)
/QSPI_SD1: U2.2 (DO_IO1), U3.55 (QSPI_SD1)
/QSPI_SD2: U2.3 (~WP_IO2), U3.54 (QSPI_SD2)
/QSPI_SD3: U2.7 (~HOLD_IO3), U3.51 (QSPI_SD3)
/QSPI_SS: R1.1, R2.2, U2.1 (~CS), U3.56 (QSPI_~SS)
/RUN: J4.29, U3.26 (RUN)
/SWCLK: J4.33, U3.24 (SWCLK)
/SWD: J4.31, U3.25 (SWD)
/USB_D+: J1.3 (D+), R3.1
/USB_D-: J1.2 (D-), R4.1
/XIN: C2.1, U3.20 (XIN), X1.1
/XOUT: R5.2, U3.21 (XOUT)
/~USB_BOOT: J2.1, R1.2
GND: C1.2, C2.2, C3.2, C4.2, C5.2, C6.2, C7.2, C8.2, C9.2, C10.2, C11.2, C12.2, C13.2, C14.2, C15.2, C16.2, C17.2, J1.5 (GND), J1.6 (SH), J1.7 (SH), J1.8 (SH), J1.9 (SH), J1.10 (SH), J1.11 (SH), J2.2, J3.1, J3.3, J3.5, J3.7, J3.9, J3.11, J3.13, J3.15, J3.17, J3.19, J3.21, J3.23, J3.25, J3.27, J3.29, J3.31, J3.33, J3.35, J3.36, J4.2, J4.4, J4.6, J4.8, J4.10, J4.12, J4.14, J4.16, J4.18, J4.20, J4.22, J4.24, J4.26, J4.28, J4.30, J4.32, J4.34, J4.35, J4.36, U1.1 (GND), U2.4 (GND), U3.19 (TESTEN), U3.57 (GND), X1.2, X1.4
unnamed: C3.1, R5.1, X1.3
unnamed: R4.2, U3.46 (USB_DM)
unnamed: R3.2, U3.47 (USB_DP)
VBUS: C1.1, J1.1 (VCC), U1.3 (IN)

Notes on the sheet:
IOs
Power
Crystal
Make sure C8 is close to pin 45 of RP2040
Make sure C10 is close to pin 44 of RP2040
Note: S1 schematic revision indicates that this is the 1st revision of the schematic/BOM associated with the R3 PCB. R3-S1 therefore uniquely identifies the fully built PCB Assembly (PCBA). This is a change from the previous revision numbering to align with the internal Raspberry Pi product revisio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
Make sure R3 and R4 are close to RP2040
Flash
